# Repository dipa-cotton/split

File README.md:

# split
my split keyboard!

## journals
https://stardance.hackclub.com/projects/28331
check out stardance for my journals!

## purpose
i wanted to make a keyboard that tracks biometric data, like heart rate, temperature, and other things using multiple sensors :) it also has a LOT more keys than your average keyboard, and will be a lot more comfortable to use.

## components
the main files are my PCB and Schematic made in kicad, and I have directories of my code as well :)

## BOM
- 100 capacitors
- 100 diodes
- 100 SK6812minis
- 2 XIAO-nRF52840-Plus-SMD
- 2 Olimex_MOD-WIFI-ESP8266-DEV
- 95 SW_Push (cherry mx switches)
- 2 max30102
- 2 tmp102
- 8 FSR
- 2 GSR
- 2 rotary encoders

## pictures
### right side:

### left side:

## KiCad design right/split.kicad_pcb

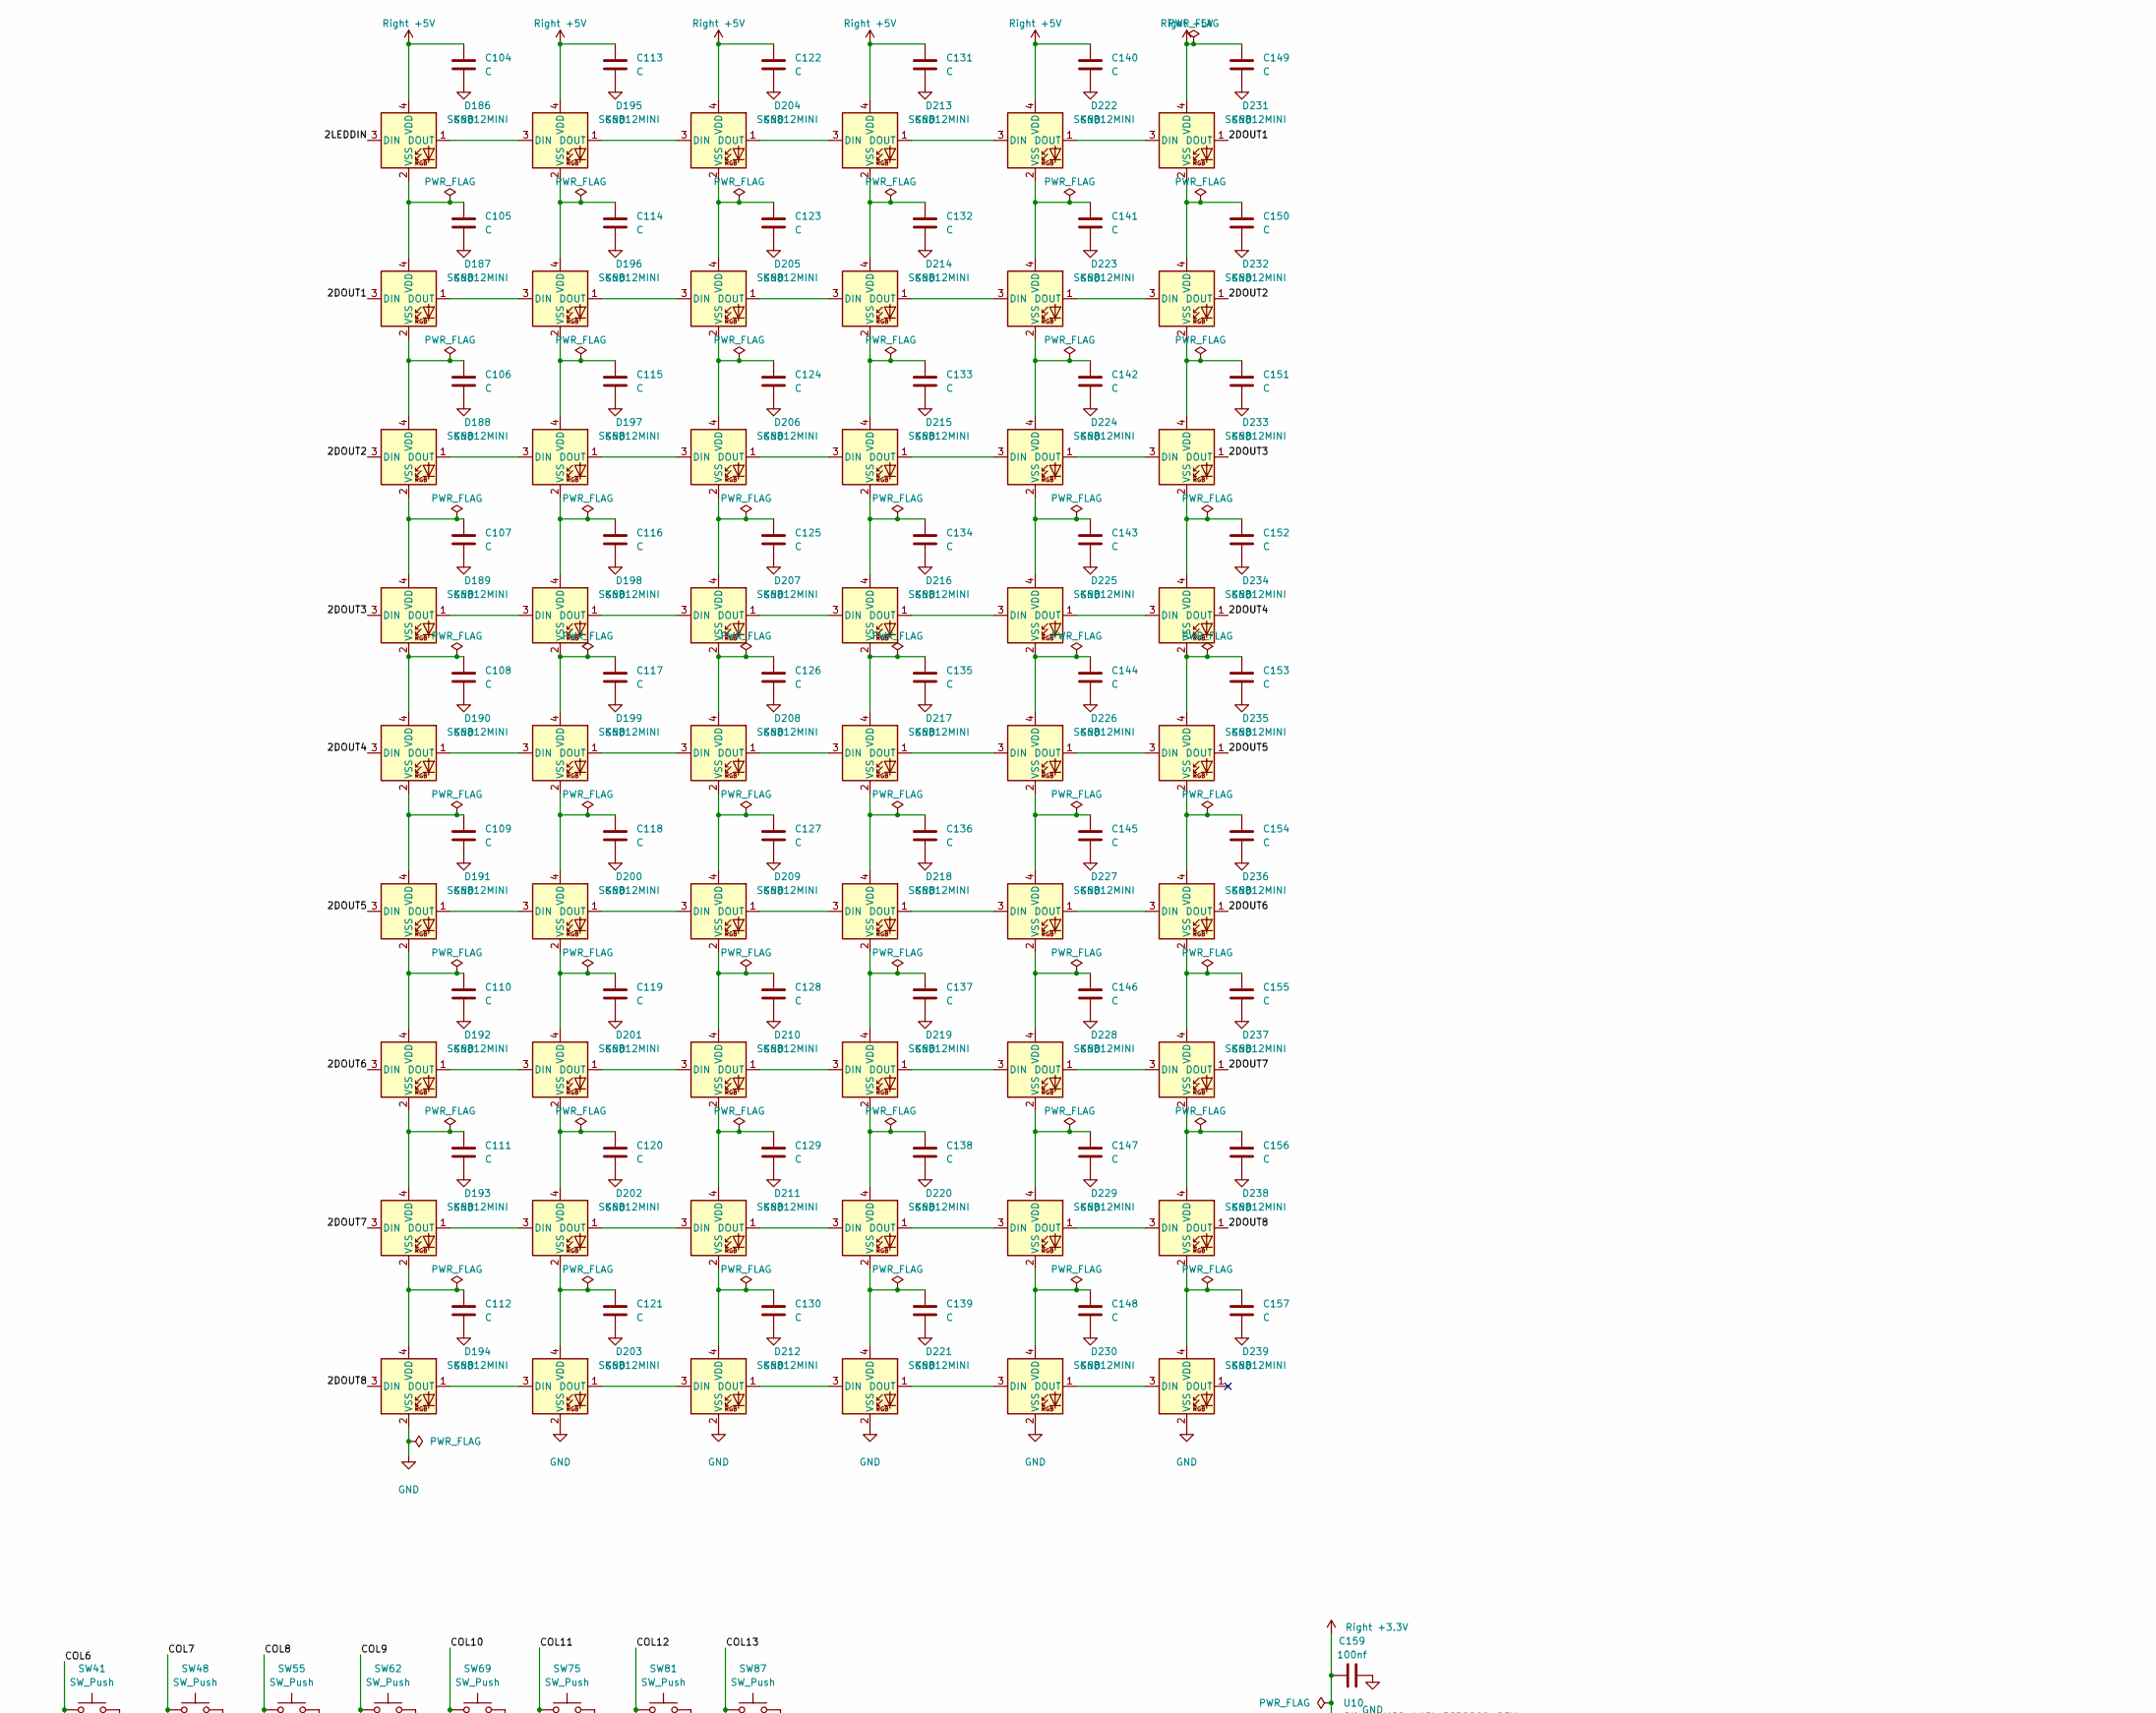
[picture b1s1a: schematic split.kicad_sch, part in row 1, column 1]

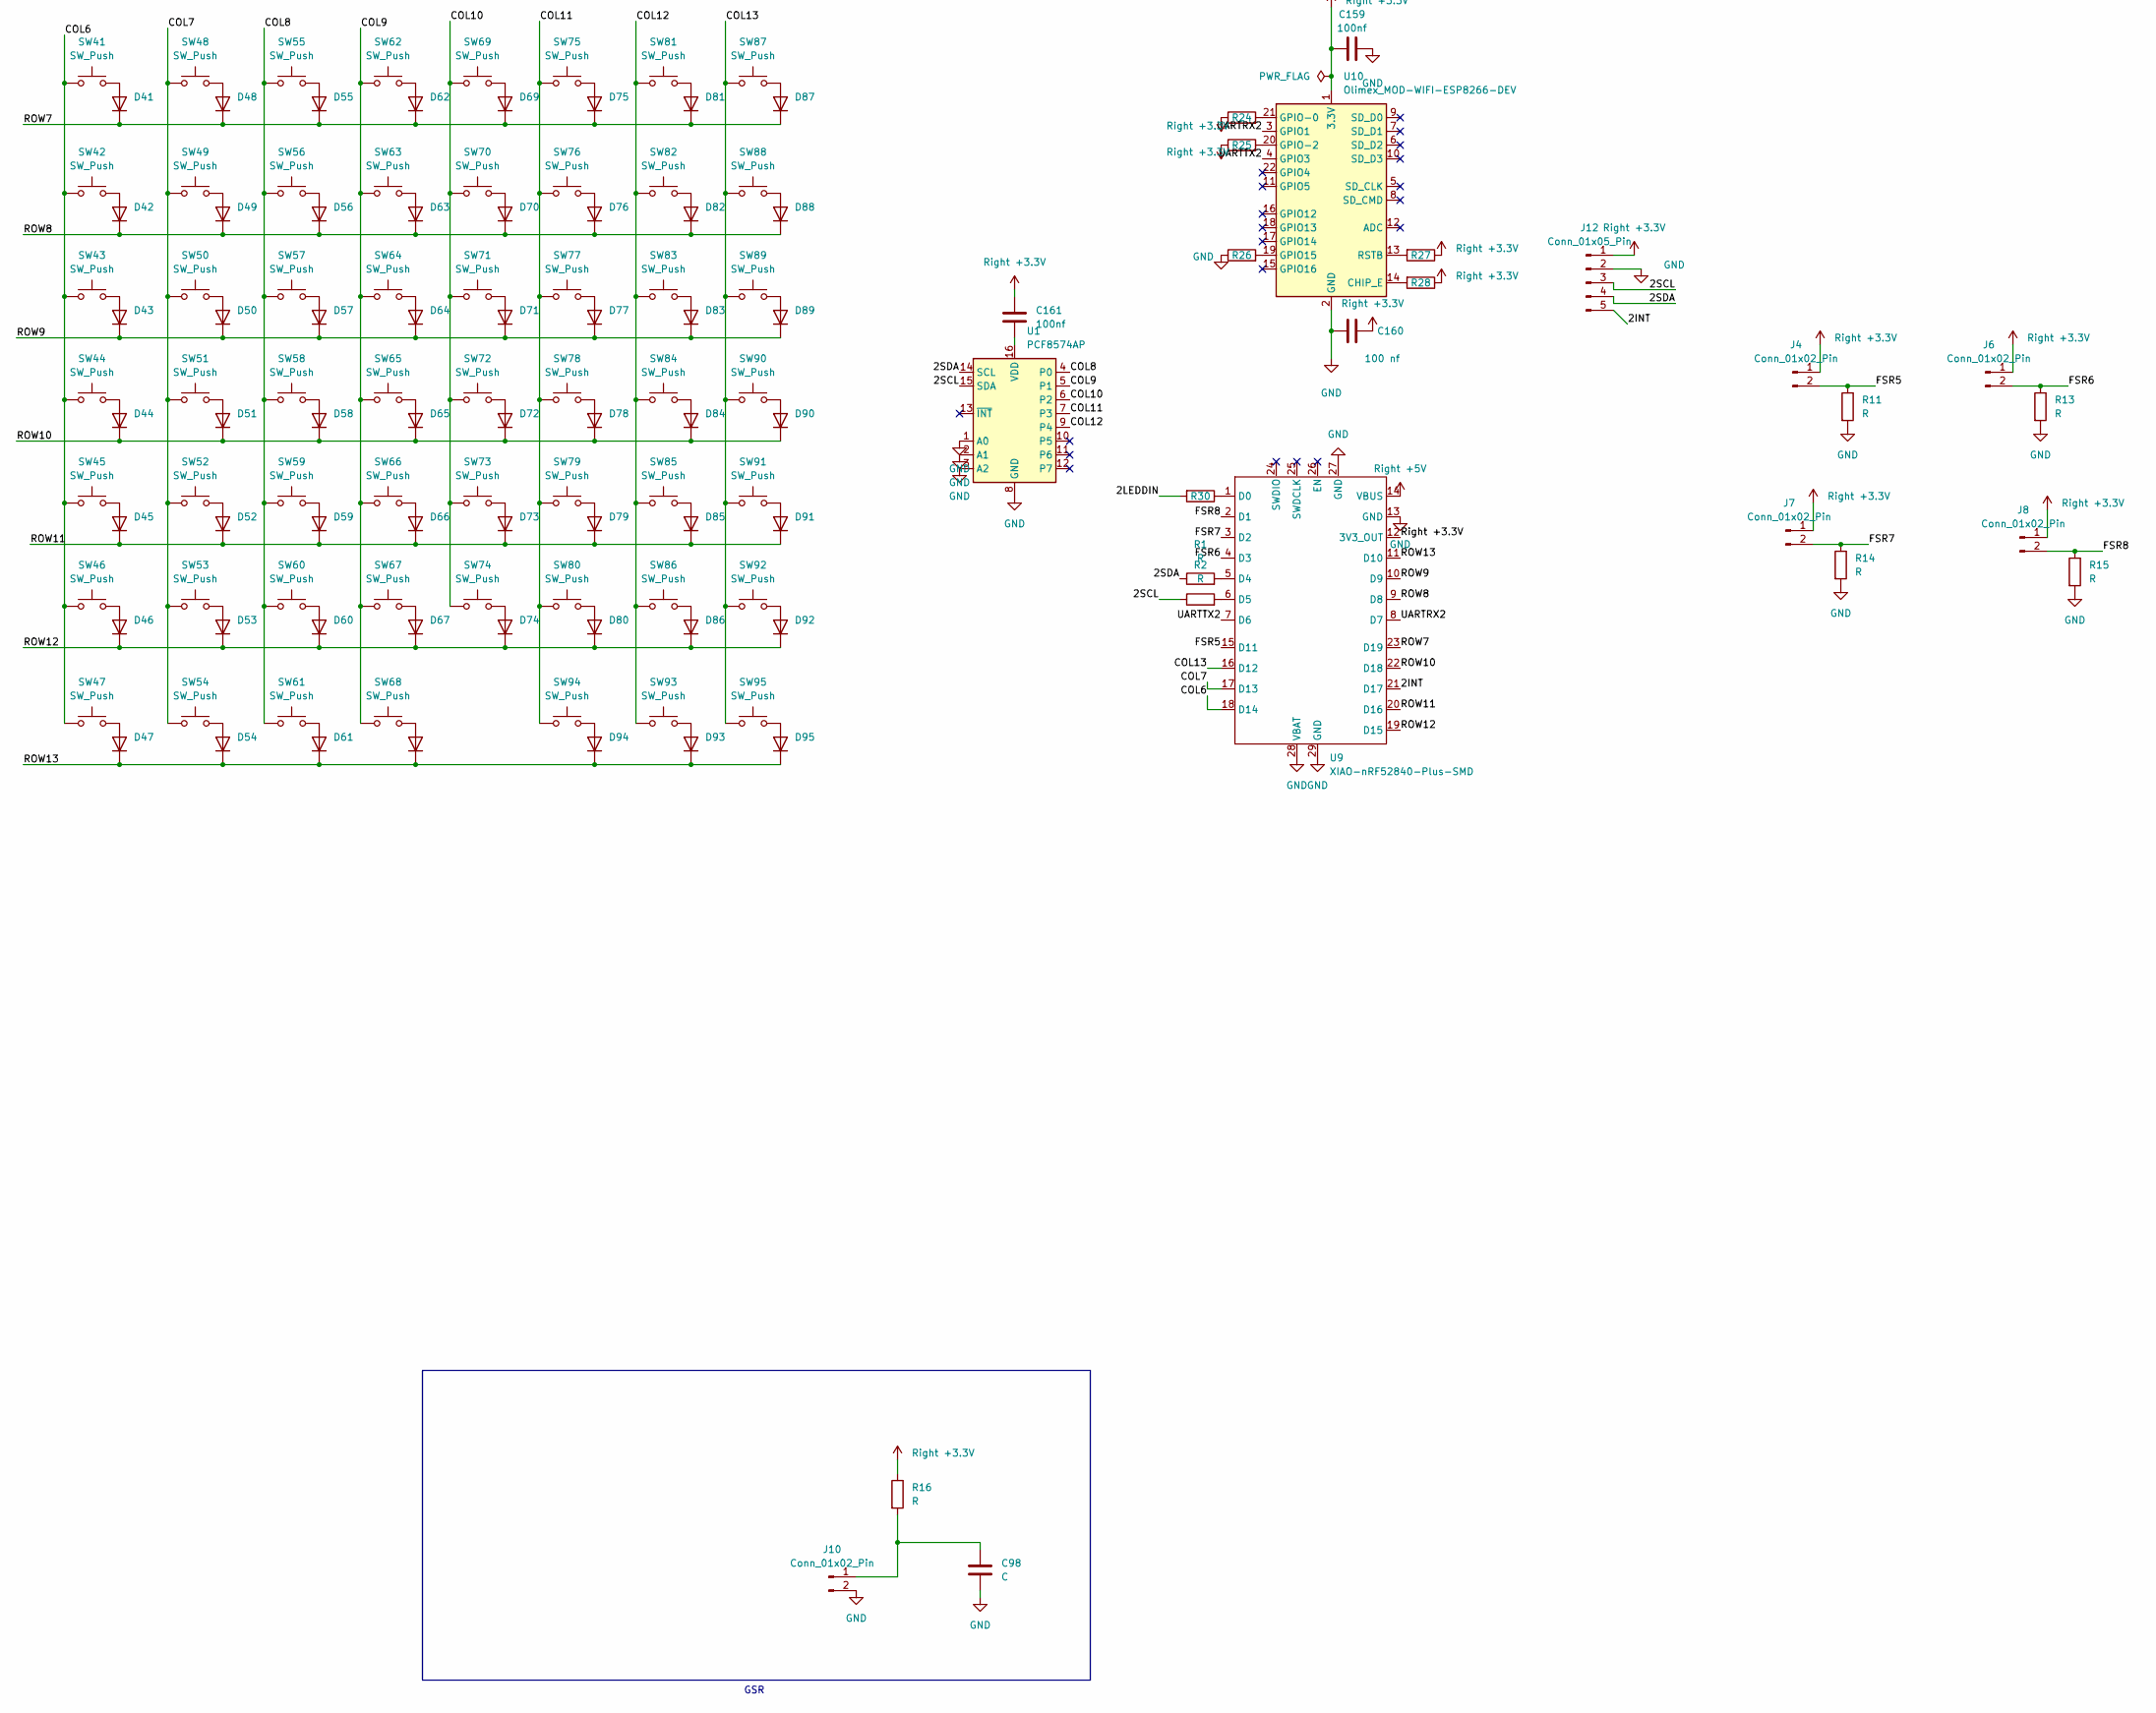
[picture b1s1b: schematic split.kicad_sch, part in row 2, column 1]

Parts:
C98, C104, C105, C106, C107, C108, C109, C110, C111, C112, C113, C114, C115, C116, C117, C118, C119, C120, C121, C122, C123, C124, C125, C126, C127, C128, C129, C130, C131, C132, C133, C134, C135, C136, C137, C138, C139, C140, C141, C142, C143, C144, C145, C146, C147, C148, C149, C150, C151, C152, C153, C154, C155, C156, C157: C; C_0603_1608Metric
C159, C161: 100nf; C_0603_1608Metric
C160: 100 nf; C_0603_1608Metric
D41, D42, D43, D44, D45, D46, D47, D48, D49, D50, D51, D52, D53, D54, D55, D56, D57, D58, D59, D60, D61, D62, D63, D64, D65, D66, D67, D68, D69, D70, D71, D72, D73, D74, D75, D76, D77, D78, D79, D80, D81, D82, D83, D84, D85, D86, D87, D88, D89, D90, D91, D92, D93, D94, D95: 1N914; C_0603_1608Metric
D186, D187, D188, D189, D190, D191, D192, D193, D194, D195, D196, D197, D198, D199, D200, D201, D202, D203, D204, D205, D206, D207, D208, D209, D210, D211, D212, D213, D214, D215, D216, D217, D218, D219, D220, D221, D222, D223, D224, D225, D226, D227, D228, D229, D230, D231, D232, D233, D234, D235, D236, D237, D238, D239: SK6812MINI; LED_SK6812MINI_PLCC4_3.5x3.5mm_P1.75mm
J4, J6, J7, J8, J10: Conn_01x02_Pin; TestPoint_Bridge_Pitch2.54mm_Drill1.0mm
J12: Conn_01x05_Pin; PinSocket_1x05_P2.54mm_Vertical
R1, R2, R11, R13, R14, R15, R16, R24, R25, R26, R27, R28, R30: R; C_0603_1608Metric
SW41, SW42, SW43, SW44, SW45, SW46, SW47, SW48, SW49, SW50, SW51, SW52, SW53, SW54, SW55, SW56, SW57, SW58, SW59, SW60, SW61, SW62, SW63, SW64, SW65, SW66, SW67, SW68, SW69, SW70, SW71, SW72, SW73, SW74, SW75, SW76, SW77, SW78, SW79, SW80, SW81, SW82, SW83, SW84, SW85, SW86, SW87, SW88, SW89, SW90, SW91, SW92, SW93, SW94, SW95: SW_Push; SW_Cherry_MX_1.00u_PCB
U1: PCF8574AP; DIP-16_W7.62mm
U9: XIAO-nRF52840-Plus-SMD
U10: Olimex_MOD-WIFI-ESP8266-DEV

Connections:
/2DOUT1: D187.3 (DIN), D231.1 (DOUT)
/2DOUT2: D188.3 (DIN), D232.1 (DOUT)
/2DOUT3: D189.3 (DIN), D233.1 (DOUT)
/2DOUT4: D190.3 (DIN), D234.1 (DOUT)
/2DOUT5: D191.3 (DIN), D235.1 (DOUT)
/2DOUT6: D192.3 (DIN), D236.1 (DOUT)
/2DOUT7: D193.3 (DIN), D237.1 (DOUT)
/2DOUT8: D194.3 (DIN), D238.1 (DOUT)
/2INT: J12.5, U9.21 (D17)
/2LEDDIN: D186.3 (DIN), R30.2
/2SCL: J12.3, R2.1, U1.15 (SDA)
/2SDA: J12.4, R1.1, U1.14 (SCL)
/COL6: SW41.1, SW42.1, SW43.1, SW44.1, SW45.1, SW46.1, SW47.1, U9.18 (D14)
/COL7: SW48.1, SW49.1, SW50.1, SW51.1, SW52.1, SW53.1, SW54.1, U9.17 (D13)
/COL8: SW55.1, SW56.1, SW57.1, SW58.1, SW59.1, SW60.1, SW61.1, U1.4 (P0)
/COL9: SW62.1, SW63.1, SW64.1, SW65.1, SW66.1, SW67.1, SW68.1, U1.5 (P1)
/COL10: SW69.1, SW70.1, SW71.1, SW72.1, SW73.1, SW74.1, U1.6 (P2)
/COL11: SW75.1, SW76.1, SW77.1, SW78.1, SW79.1, SW80.1, SW94.1, U1.7 (P3)
/COL12: SW81.1, SW82.1, SW83.1, SW84.1, SW85.1, SW86.1, SW93.1, U1.9 (P4)
/COL13: SW87.1, SW88.1, SW89.1, SW90.1, SW91.1, SW92.1, SW95.1, U9.16 (D12)
/FSR5: J4.2, R11.1, U9.15 (D11)
/FSR6: J6.2, R13.1, U9.4 (D3)
/FSR7: J7.2, R14.1, U9.3 (D2)
/FSR8: J8.2, R15.1, U9.2 (D1)
/ROW7: D41.1 (K), D48.1 (K), D55.1 (K), D62.1 (K), D69.1 (K), D75.1 (K), D81.1 (K), D87.1 (K), U9.23 (D19)
/ROW8: D42.1 (K), D49.1 (K), D56.1 (K), D63.1 (K), D70.1 (K), D76.1 (K), D82.1 (K), D88.1 (K), U9.9 (D8)
/ROW9: D43.1 (K), D50.1 (K), D57.1 (K), D64.1 (K), D71.1 (K), D77.1 (K), D83.1 (K), D89.1 (K), U9.10 (D9)
/ROW10: D44.1 (K), D51.1 (K), D58.1 (K), D65.1 (K), D72.1 (K), D78.1 (K), D84.1 (K), D90.1 (K), U9.22 (D18)
/ROW11: D45.1 (K), D52.1 (K), D59.1 (K), D66.1 (K), D73.1 (K), D79.1 (K), D85.1 (K), D91.1 (K), U9.20 (D16)
/ROW12: D46.1 (K), D53.1 (K), D60.1 (K), D67.1 (K), D74.1 (K), D80.1 (K), D86.1 (K), D92.1 (K), U9.19 (D15)
/ROW13: D47.1 (K), D54.1 (K), D61.1 (K), D68.1 (K), D93.1 (K), D94.1 (K), D95.1 (K), U9.11 (D10)
/UARTRX2: U9.8 (D7), U10.3 (GPIO1)
/UARTTX2: U9.7 (D6), U10.4 (GPIO3)
GND: C98.2, C104.2, C105.2, C106.2, C107.2, C108.2, C109.2, C110.2, C111.2, C112.2, C113.2, C114.2, C115.2, C116.2, C117.2, C118.2, C119.2, C120.2, C121.2, C122.2, C123.2, C124.2, C125.2, C126.2, C127.2, C128.2, C129.2, C130.2, C131.2, C132.2, C133.2, C134.2, C135.2, C136.2, C137.2, C138.2, C139.2, C140.2, C141.2, C142.2, C143.2, C144.2, C145.2, C146.2, C147.2, C148.2, C149.2, C150.2, C151.2, C152.2, C153.2, C154.2, C155.2, C156.2, C157.2, C159.1, C160.2, D194.2 (VSS), D203.2 (VSS), D212.2 (VSS), D221.2 (VSS), D230.2 (VSS), D239.2 (VSS), J10.2, J12.2, R11.2, R13.2, R14.2, R15.2, R26.1, U1.1 (A0), U1.2 (A1), U1.3 (A2), U1.8 (GND), U9.13 (GND), U9.27 (GND), U9.28 (VBAT), U9.29 (GND), U10.2 (GND)
unnamed: D41.2 (A), SW41.2
unnamed: D42.2 (A), SW42.2
unnamed: D43.2 (A), SW43.2
unnamed: D44.2 (A), SW44.2
unnamed: D45.2 (A), SW45.2
unnamed: D46.2 (A), SW46.2
unnamed: D47.2 (A), SW47.2
unnamed: D48.2 (A), SW48.2
unnamed: D49.2 (A), SW49.2
unnamed: D50.2 (A), SW50.2
unnamed: D51.2 (A), SW51.2
unnamed: D52.2 (A), SW52.2
unnamed: D53.2 (A), SW53.2
unnamed: D54.2 (A), SW54.2
unnamed: D55.2 (A), SW55.2
unnamed: D56.2 (A), SW56.2
unnamed: D57.2 (A), SW57.2
unnamed: D58.2 (A), SW58.2
unnamed: D59.2 (A), SW59.2
unnamed: D60.2 (A), SW60.2
unnamed: D61.2 (A), SW61.2
unnamed: D62.2 (A), SW62.2
unnamed: D63.2 (A), SW63.2
unnamed: D64.2 (A), SW64.2
unnamed: D65.2 (A), SW65.2
unnamed: D66.2 (A), SW66.2
unnamed: D67.2 (A), SW67.2
unnamed: D68.2 (A), SW68.2
unnamed: D69.2 (A), SW69.2
unnamed: D70.2 (A), SW70.2
unnamed: D71.2 (A), SW71.2
unnamed: D72.2 (A), SW72.2
unnamed: D73.2 (A), SW73.2
unnamed: D74.2 (A), SW74.2
unnamed: D75.2 (A), SW75.2
unnamed: D76.2 (A), SW76.2
unnamed: D77.2 (A), SW77.2
unnamed: D78.2 (A), SW78.2
unnamed: D79.2 (A), SW79.2
unnamed: D80.2 (A), SW80.2
unnamed: D81.2 (A), SW81.2
unnamed: D82.2 (A), SW82.2
unnamed: D83.2 (A), SW83.2
unnamed: D84.2 (A), SW84.2
unnamed: D85.2 (A), SW85.2
unnamed: D86.2 (A), SW86.2
unnamed: D87.2 (A), SW87.2
unnamed: D88.2 (A), SW88.2
unnamed: D89.2 (A), SW89.2
unnamed: D90.2 (A), SW90.2
unnamed: D91.2 (A), SW91.2
unnamed: D92.2 (A), SW92.2
unnamed: D93.2 (A), SW93.2
unnamed: D94.2 (A), SW94.2
unnamed: D95.2 (A), SW95.2
unnamed: D186.1 (DOUT), D195.3 (DIN)
unnamed: C105.1, D186.2 (VSS), D187.4 (VDD)
unnamed: D187.1 (DOUT), D196.3 (DIN)
unnamed: C106.1, D187.2 (VSS), D188.4 (VDD)
unnamed: D188.1 (DOUT), D197.3 (DIN)
unnamed: C107.1, D188.2 (VSS), D189.4 (VDD)
unnamed: D189.1 (DOUT), D198.3 (DIN)
unnamed: C108.1, D189.2 (VSS), D190.4 (VDD)
unnamed: D190.1 (DOUT), D199.3 (DIN)
unnamed: C109.1, D190.2 (VSS), D191.4 (VDD)
unnamed: D191.1 (DOUT), D200.3 (DIN)
unnamed: C110.1, D191.2 (VSS), D192.4 (VDD)
unnamed: D192.1 (DOUT), D201.3 (DIN)
unnamed: C111.1, D192.2 (VSS), D193.4 (VDD)
unnamed: D193.1 (DOUT), D202.3 (DIN)
unnamed: C112.1, D193.2 (VSS), D194.4 (VDD)
unnamed: D194.1 (DOUT), D203.3 (DIN)
unnamed: D195.1 (DOUT), D204.3 (DIN)
unnamed: C114.1, D195.2 (VSS), D196.4 (VDD)
unnamed: D196.1 (DOUT), D205.3 (DIN)
unnamed: C115.1, D196.2 (VSS), D197.4 (VDD)
unnamed: D197.1 (DOUT), D206.3 (DIN)
unnamed: C116.1, D197.2 (VSS), D198.4 (VDD)
unnamed: D198.1 (DOUT), D207.3 (DIN)
unnamed: C117.1, D198.2 (VSS), D199.4 (VDD)
unnamed: D199.1 (DOUT), D208.3 (DIN)
unnamed: C118.1, D199.2 (VSS), D200.4 (VDD)
unnamed: D200.1 (DOUT), D209.3 (DIN)
unnamed: C119.1, D200.2 (VSS), D201.4 (VDD)
unnamed: D201.1 (DOUT), D210.3 (DIN)
unnamed: C120.1, D201.2 (VSS), D202.4 (VDD)
unnamed: D202.1 (DOUT), D211.3 (DIN)
unnamed: C121.1, D202.2 (VSS), D203.4 (VDD)
unnamed: D203.1 (DOUT), D212.3 (DIN)
unnamed: D204.1 (DOUT), D213.3 (DIN)
unnamed: C123.1, D204.2 (VSS), D205.4 (VDD)
unnamed: D205.1 (DOUT), D214.3 (DIN)
unnamed: C124.1, D205.2 (VSS), D206.4 (VDD)
unnamed: D206.1 (DOUT), D215.3 (DIN)
unnamed: C125.1, D206.2 (VSS), D207.4 (VDD)
unnamed: D207.1 (DOUT), D216.3 (DIN)
unnamed: C126.1, D207.2 (VSS), D208.4 (VDD)
unnamed: D208.1 (DOUT), D217.3 (DIN)
unnamed: C127.1, D208.2 (VSS), D209.4 (VDD)
unnamed: D209.1 (DOUT), D218.3 (DIN)
unnamed: C128.1, D209.2 (VSS), D210.4 (VDD)
unnamed: D210.1 (DOUT), D219.3 (DIN)
unnamed: C129.1, D210.2 (VSS), D211.4 (VDD)
unnamed: D211.1 (DOUT), D220.3 (DIN)
unnamed: C130.1, D211.2 (VSS), D212.4 (VDD)
unnamed: D212.1 (DOUT), D221.3 (DIN)
unnamed: D213.1 (DOUT), D222.3 (DIN)
unnamed: C132.1, D213.2 (VSS), D214.4 (VDD)
unnamed: D214.1 (DOUT), D223.3 (DIN)
unnamed: C133.1, D214.2 (VSS), D215.4 (VDD)
unnamed: D215.1 (DOUT), D224.3 (DIN)
unnamed: C134.1, D215.2 (VSS), D216.4 (VDD)
unnamed: D216.1 (DOUT), D225.3 (DIN)
unnamed: C135.1, D216.2 (VSS), D217.4 (VDD)
unnamed: D217.1 (DOUT), D226.3 (DIN)
unnamed: C136.1, D217.2 (VSS), D218.4 (VDD)
unnamed: D218.1 (DOUT), D227.3 (DIN)
unnamed: C137.1, D218.2 (VSS), D219.4 (VDD)
unnamed: D219.1 (DOUT), D228.3 (DIN)
unnamed: C138.1, D219.2 (VSS), D220.4 (VDD)
unnamed: D220.1 (DOUT), D229.3 (DIN)
unnamed: C139.1, D220.2 (VSS), D221.4 (VDD)
unnamed: D221.1 (DOUT), D230.3 (DIN)
unnamed: D222.1 (DOUT), D231.3 (DIN)
unnamed: C141.1, D222.2 (VSS), D223.4 (VDD)
unnamed: D223.1 (DOUT), D232.3 (DIN)
unnamed: C142.1, D223.2 (VSS), D224.4 (VDD)
unnamed: D224.1 (DOUT), D233.3 (DIN)
unnamed: C143.1, D224.2 (VSS), D225.4 (VDD)
unnamed: D225.1 (DOUT), D234.3 (DIN)
unnamed: C144.1, D225.2 (VSS), D226.4 (VDD)
unnamed: D226.1 (DOUT), D235.3 (DIN)
unnamed: C145.1, D226.2 (VSS), D227.4 (VDD)
unnamed: D227.1 (DOUT), D236.3 (DIN)
unnamed: C146.1, D227.2 (VSS), D228.4 (VDD)
unnamed: D228.1 (DOUT), D237.3 (DIN)
unnamed: C147.1, D228.2 (VSS), D229.4 (VDD)
unnamed: D229.1 (DOUT), D238.3 (DIN)
unnamed: C148.1, D229.2 (VSS), D230.4 (VDD)
unnamed: D230.1 (DOUT), D239.3 (DIN)
unnamed: C150.1, D231.2 (VSS), D232.4 (VDD)
unnamed: C151.1, D232.2 (VSS), D233.4 (VDD)
unnamed: C152.1, D233.2 (VSS), D234.4 (VDD)
unnamed: C153.1, D234.2 (VSS), D235.4 (VDD)
unnamed: C154.1, D235.2 (VSS), D236.4 (VDD)
unnamed: C155.1, D236.2 (VSS), D237.4 (VDD)
unnamed: C156.1, D237.2 (VSS), D238.4 (VDD)
unnamed: C157.1, D238.2 (VSS), D239.4 (VDD)
unnamed: C98.1, J10.1 (Pin_1_1), R16.2
unnamed: C161.2, U1.16 (VDD)
unnamed: R30.1, U9.1 (D0)
unnamed: R1.2, U9.5 (D4)
unnamed: R2.2, U9.6 (D5)
unnamed: R28.2, U10.14 (CHIP_E)
unnamed: R26.2, U10.19 (GPIO15)
unnamed: R24.2, U10.21 (GPIO-0)
unnamed: R25.2, U10.20 (GPIO-2)
unnamed: R27.2, U10.13 (RSTB)
Right +3.3V: C159.2, C160.1, C161.1, J4.1 (Pin_1_1), J6.1 (Pin_1_1), J7.1 (Pin_1_1), J8.1 (Pin_1_1), J12.1, R16.1, R24.1, R25.1, R27.1, R28.1, U9.12 (3V3_OUT), U10.1 (3.3V)
Right +5V: C104.1, C113.1, C122.1, C131.1, C140.1, C149.1, D186.4 (VDD), D195.4 (VDD), D204.4 (VDD), D213.4 (VDD), D222.4 (VDD), D231.4 (VDD), U9.14 (VBUS)

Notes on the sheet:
GSR

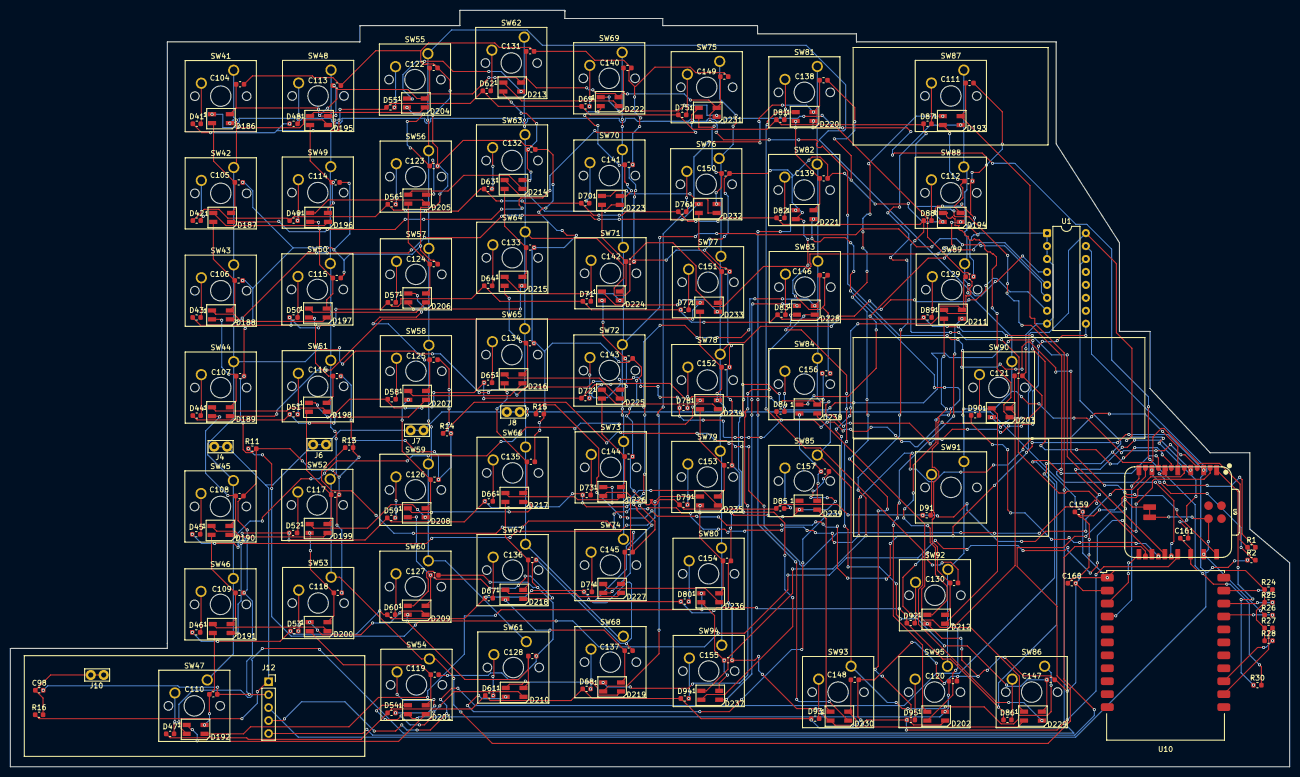
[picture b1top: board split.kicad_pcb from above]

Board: 2 copper layers, 251.0 x 148.4 mm, 244 parts (0 on the bottom side), 194 nets.
